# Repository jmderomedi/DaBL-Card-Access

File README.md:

Access to the AU Design and Build Lab (DaBL) machines via RFID cards.

This system has two utilities:
	[1] Badge-in, badge-out at the main station for safety waiver confirmation and data gathering
	[2] Limiting access to machine-specific computers (eg. 3D printers, Bantam Tools mill)

Current version functionality:
	- Periodic (1sec) communication between Teensy and python script to make sure they don't lose contact
	- Teensy reads RFID UID and sends to python
	- Python is very basically communicating with database

To do:
	- set up database (called "DaBL") structure:
		[1] table: "access logs" (for main station)
			name | UID | timestamp
		[2] table: "users" (for machine-specfic access)
			name | UID | membersince | lastvisit | waiver | series1pro | uprintseplus | bantamtools | pls475
	- flesh out database commands (currently only READs are coded)

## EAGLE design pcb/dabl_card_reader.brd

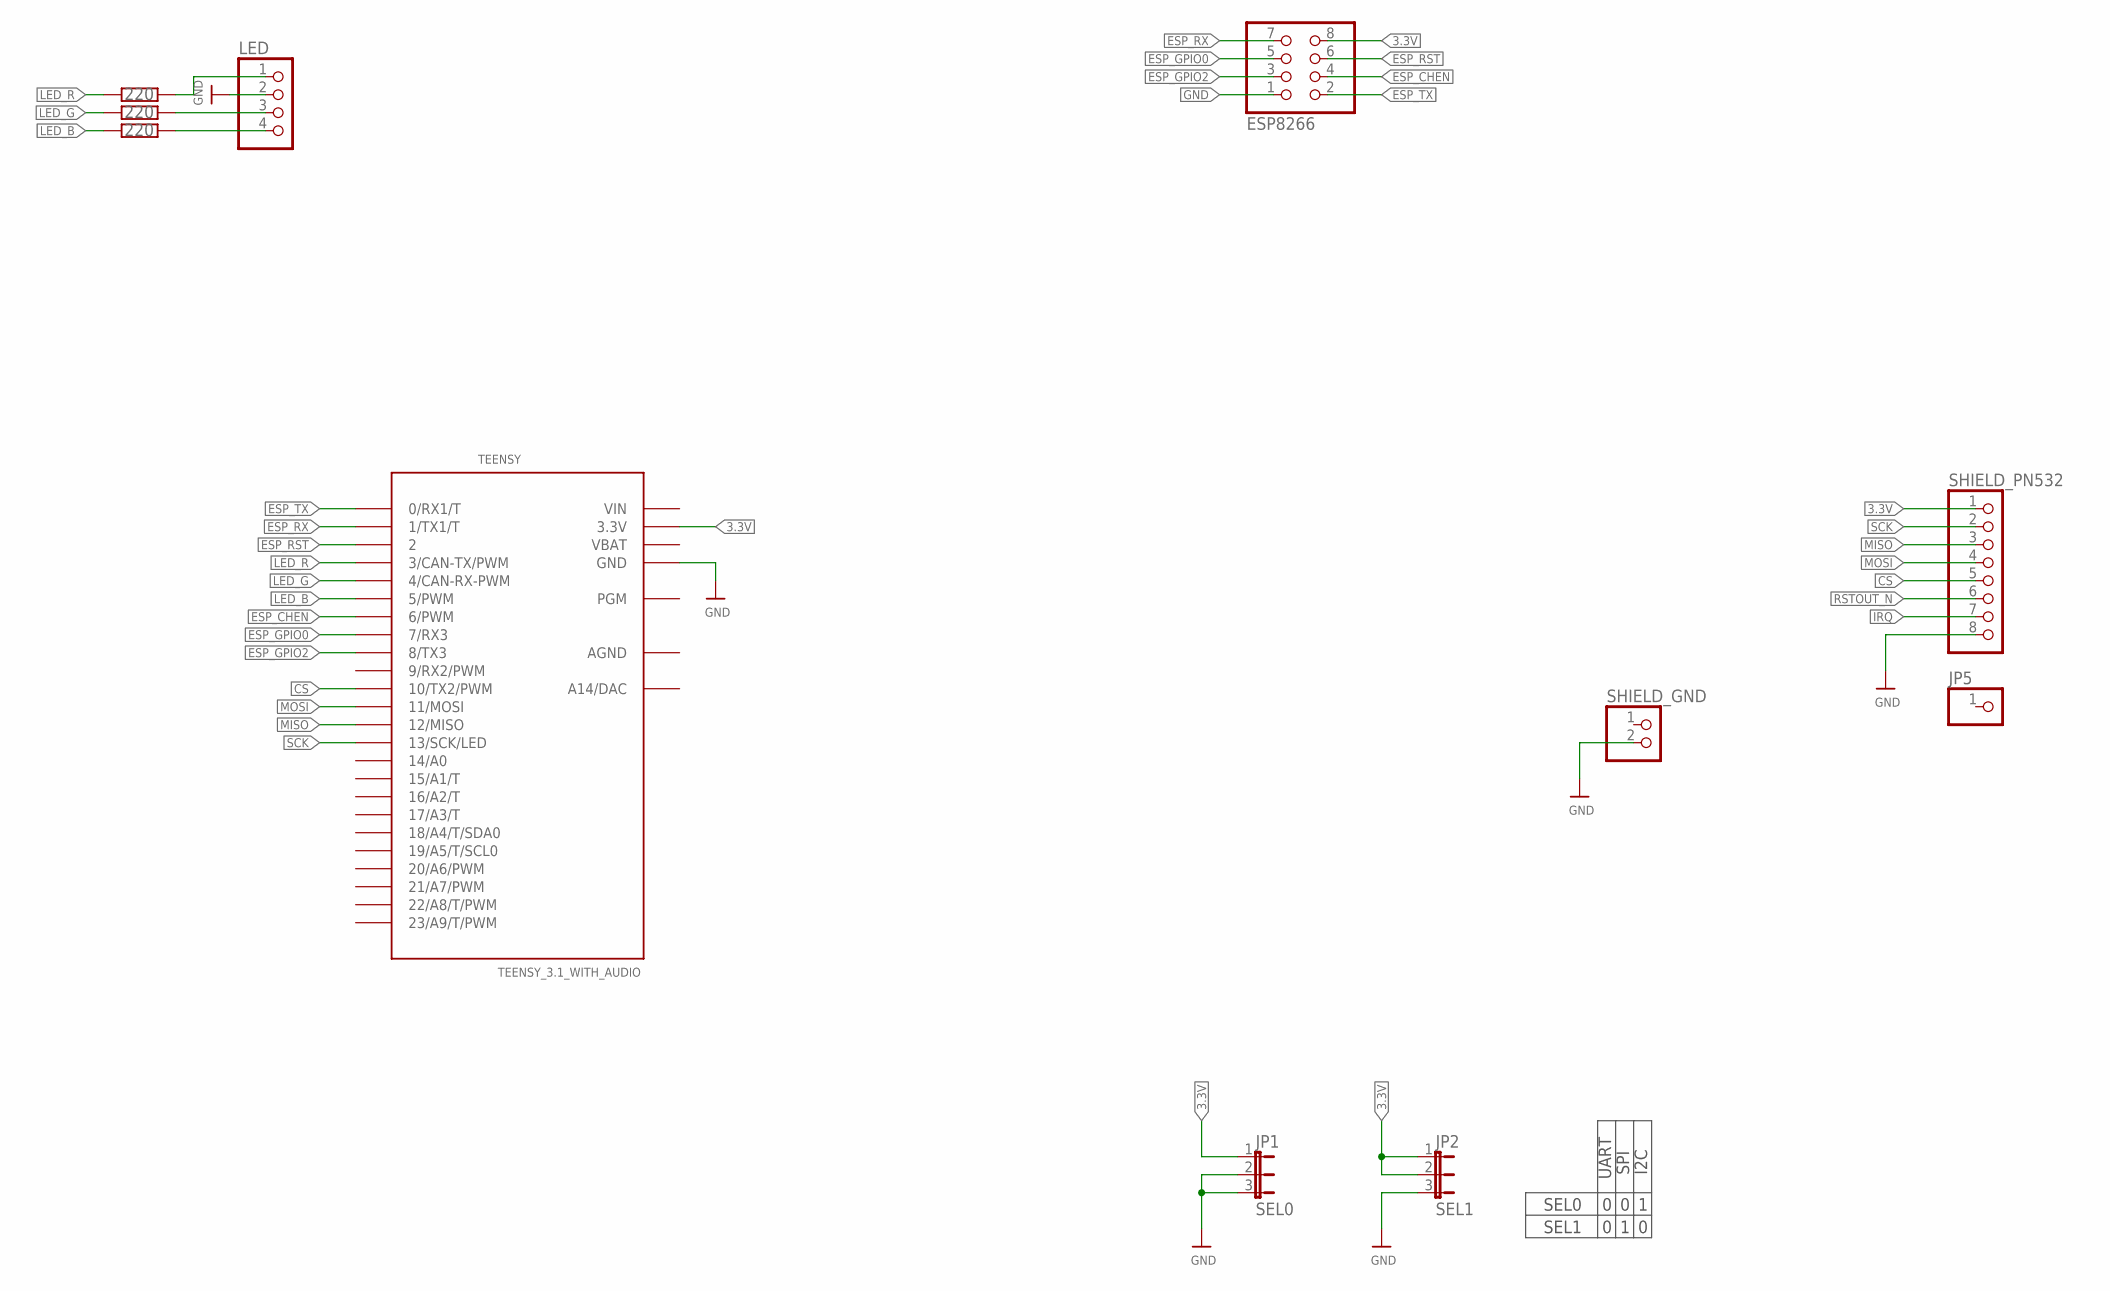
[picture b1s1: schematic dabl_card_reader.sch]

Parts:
ESP8266: PINHD-2X4; 2X04
JP1: SEL0; JUMPER3
JP2: SEL1; JUMPER3
JP5: HEADER-1X1ROUND; 1X01_ROUND
LED: PINHD-1X4; 1X04
R1, R2, R3: 220; M0805
SHIELD_GND: PINHD-1X2; 1X02
SHIELD_PN532: HEADER-1X8ROUND; 1X08_ROUND
TEENSY: TEENSY_3.1_WITH_AUDIO; TEENSY_3.2_WITH_AUDIO

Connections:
3.3V: ESP8266.8, JP1.1, JP2.1, JP2.2, SHIELD_PN532.1, TEENSY.3.3V, TEENSY.3.3V1 (3.3V)
AGND: TEENSY.AGND
CS: SHIELD_PN532.5, TEENSY.10 (10/TX2/PWM)
ESP_CHEN: ESP8266.4, TEENSY.6 (6/PWM)
ESP_GPIO0: ESP8266.5, TEENSY.7 (7/RX3)
ESP_GPIO2: ESP8266.3, TEENSY.8 (8/TX3)
ESP_RST: ESP8266.6, TEENSY.2
ESP_RX: ESP8266.7, TEENSY.1 (1/TX1/T)
ESP_TX: ESP8266.2, TEENSY.0 (0/RX1/T)
GND: ESP8266.1, JP1.2, JP1.3, JP2.3, LED.2, SHIELD_GND.2, SHIELD_PN532.8, TEENSY.GND, TEENSY.GND1 (GND)
IRQ: SHIELD_PN532.7
LED_B: R3.2, TEENSY.5 (5/PWM)
LED_G: R2.2, TEENSY.4 (4/CAN-RX-PWM)
LED_R: R1.2, TEENSY.3 (3/CAN-TX/PWM)
MISO: SHIELD_PN532.3, TEENSY.12 (12/MISO)
MOSI: SHIELD_PN532.4, TEENSY.11 (11/MOSI)
unnamed: LED.4, R3.1
unnamed: LED.3, R2.1
unnamed: LED.1, R1.1
RSTOUT_N: SHIELD_PN532.6
SCK: SHIELD_PN532.2, TEENSY.13 (13/SCK/LED)
VBAT: TEENSY.VBAT
VIN: TEENSY.VIN

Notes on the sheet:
SEL0
SEL1
UART
SPI
I2C

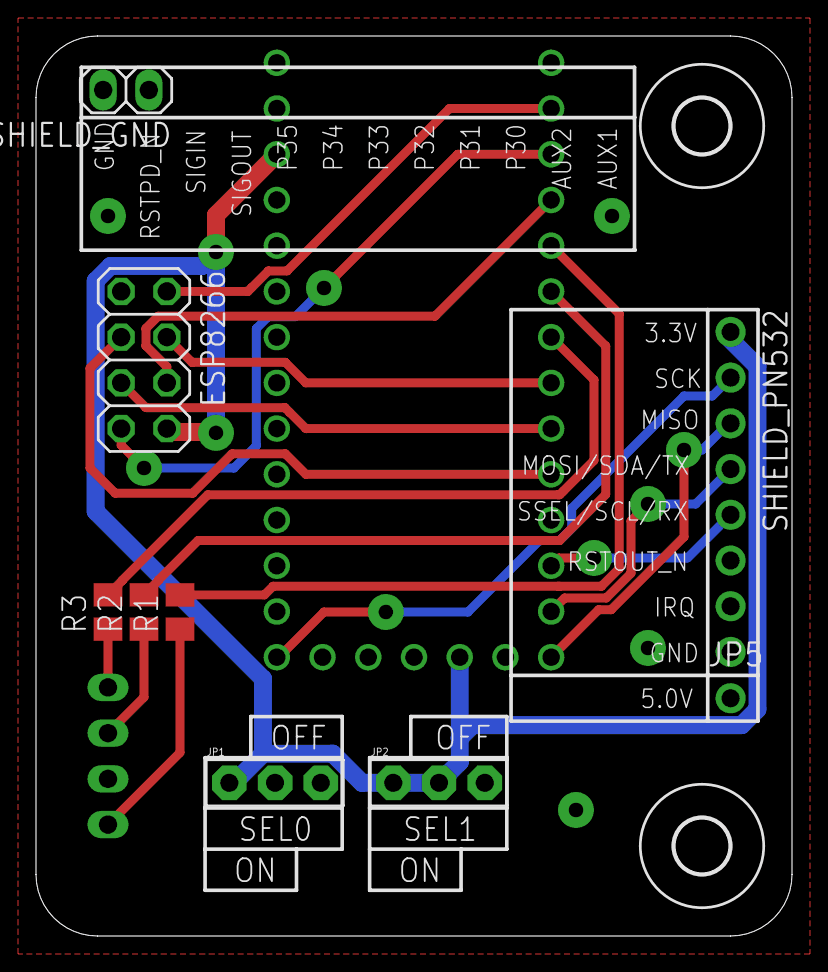
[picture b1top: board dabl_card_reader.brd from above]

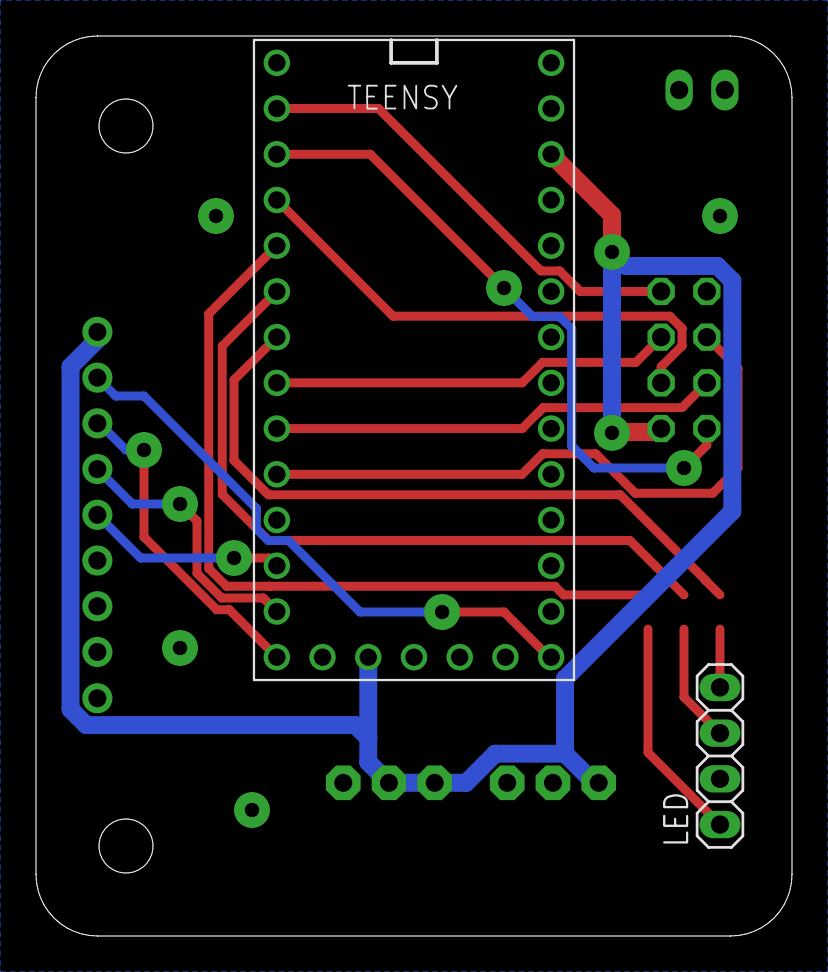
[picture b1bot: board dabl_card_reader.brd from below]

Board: 2 copper layers, 42.0 x 50.0 mm, 13 parts (2 on the bottom side), 18 nets.

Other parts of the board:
U$37, U$38: MOUNTINGHOLE_3.0

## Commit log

2018-02-10 arduino <-> python
2018-02-11 added .gitignore and initial readme
2018-02-11 added mysql-python lib
2018-02-11 working database communication
2018-02-14 fully working arduino <-> python <-> mysql with nice console output
2018-02-14 minor changes
2018-02-14 started pcb
2018-02-14 removed EAGLE backup files and included them in .gitignore
2018-02-15 pulled in PN532 board dimensions and pin layout
2018-02-15 full pcb for testing
2018-02-22 working with specific IP address
2018-05-17 fixed merge issue
2018-05-18 change hardware to teensy/esp8266/pn532; full working code minus accesslogging
2018-05-18 add sql insert functionality
2018-05-18 begin integration of time
2018-05-21 code cleanup
2018-05-21 full working logging includine UTC timestamp
2018-05-21 add LED indication support
2018-05-29 finish initial pcb design
2018-05-29 remove old python script
2018-06-29 slight refactor; change baudrate of esp8266 to 9600 to fix (AT+UART_DEF=9600,8,1,0,0)
2018-07-02 fix pcb traces
2018-07-23 fix datetimeissue
2018-09-05 Here is the front end
2018-10-05 Added a bunch of comments to make it understandable
2018-10-05 Added abstract
